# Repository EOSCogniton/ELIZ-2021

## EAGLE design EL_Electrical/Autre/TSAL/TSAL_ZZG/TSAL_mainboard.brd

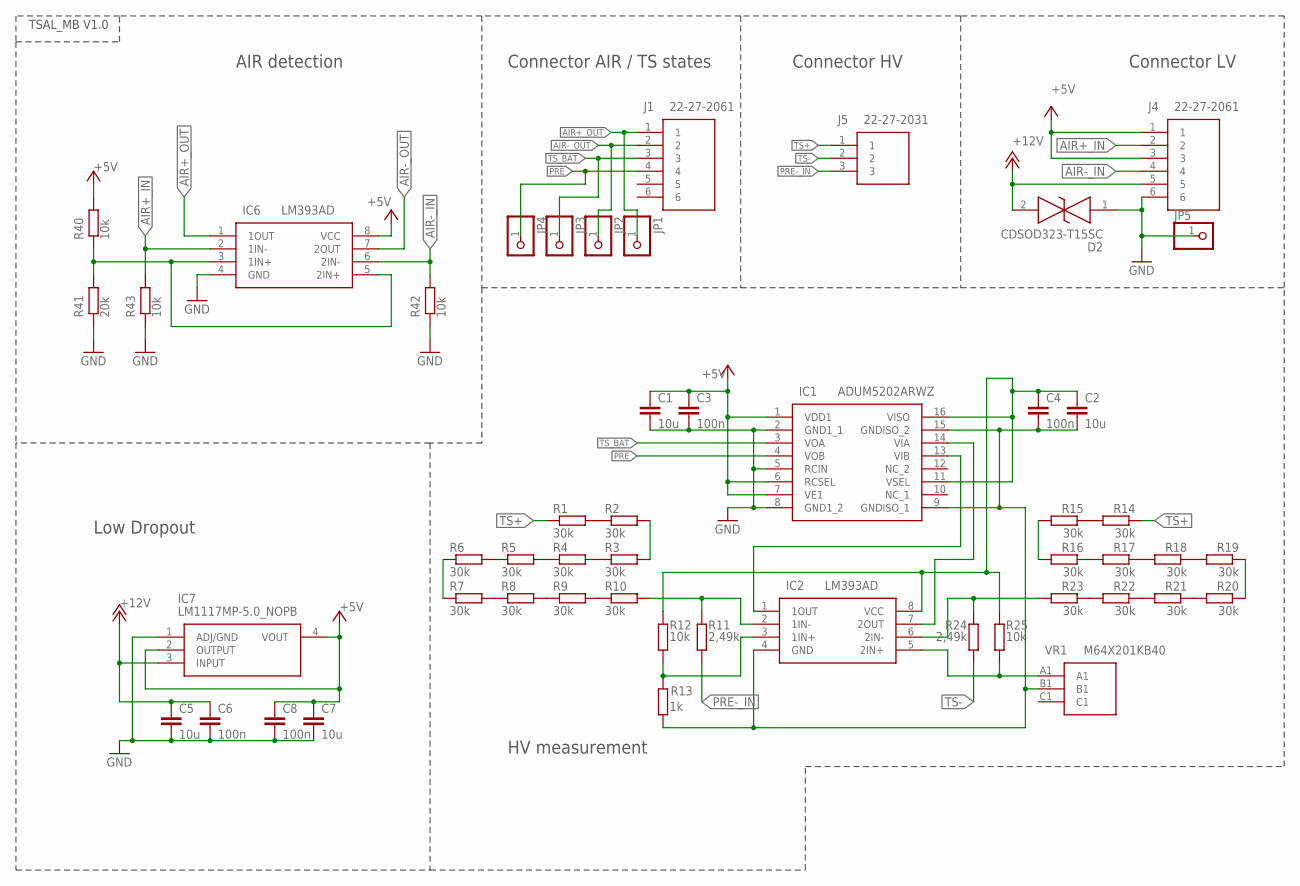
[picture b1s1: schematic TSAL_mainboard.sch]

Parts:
C1, C2, C5, C7: 10u; C1206
C3, C4, C6, C8: 100n; C0603
D2: CDSOD323-T15SC; SOD-323
IC1: ADUM5202ARWZ; SOIC127P1032X265-16N
IC2, IC6: LM393AD; SOIC127P600X175-8N
IC7: LM1117MP-5.0_NOPB; SOT230P700X180-4N
J1, J4: 22-27-2061; HDRV6W64P0X254_1X6_1524X580X11
J5: 22-27-2031; SHDR3W64P0X254_1X3_762X580X111
JP1, JP2, JP3, JP4, JP5: PINHD-1X1; 1X01
R1, R2, R3, R4, R5, R6, R7, R8, R9, R10, R14, R15, R16, R17, R18, R19, R20, R21, R22, R23: 30k; R1206
R11, R24: 2,49k; R0603
R12, R25, R40, R42, R43: 10k; R0603
R13: 1k; R1206
R41: 20k; R0603
VR1: M64X201KB40

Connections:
+5V: C1.1, C3.1, C7.1, C8.1, IC1.1 (VDD1), IC1.6 (RCSEL), IC1.7 (VE1), IC6.8 (VCC), IC7.2 (OUTPUT), IC7.4 (VOUT), J4.1, J4.3, R40.2
+12V: C5.1, C6.1, D2.2, IC7.3 (INPUT), J4.5
AIR+_IN: IC6.2 (1IN-), J4.2, R43.2
AIR+_OUT: IC6.1 (1OUT), J1.1, JP1.1
AIR-_IN: IC6.6 (2IN-), J4.4, R42.2
AIR-_OUT: IC6.7 (2OUT), J1.2, JP2.1
GND: C1.2, C3.2, C5.2, C6.2, C7.2, C8.2, D2.1, IC1.2 (GND1_1), IC1.5 (RCIN), IC1.8 (GND1_2), IC6.4 (GND), IC7.1 (ADJ/GND), J4.6, JP5.1, R41.1, R42.1, R43.1
unnamed: C2.1, C4.1, IC1.11 (VSEL), IC1.16 (VISO), IC2.8 (VCC), R12.1, R25.1
unnamed: R1.1, R2.2
unnamed: R2.1, R3.2
unnamed: R3.1, R4.2
unnamed: R4.1, R5.2
unnamed: R6.2, R7.1
unnamed: R7.2, R8.1
unnamed: R8.2, R9.1
unnamed: R9.2, R10.1
unnamed: R5.1, R6.1
unnamed: IC2.2 (1IN-), R10.2, R11.1
unnamed: IC2.3 (1IN+), R12.2, R13.1
unnamed: R14.1, R15.2
unnamed: R15.1, R16.2
unnamed: R16.1, R17.2
unnamed: R17.1, R18.2
unnamed: R19.2, R20.1
unnamed: R20.2, R21.1
unnamed: R21.2, R22.1
unnamed: R22.2, R23.1
unnamed: R18.1, R19.1
unnamed: IC2.6 (2IN-), R23.2, R24.1
unnamed: IC1.13 (VIB), IC2.1 (1OUT)
unnamed: IC2.5 (2IN+), R25.2, VR1.A1
unnamed: IC1.14 (VIA), IC2.7 (2OUT)
unnamed: IC6.3 (1IN+), IC6.5 (2IN+), R40.1, R41.2
unnamed: C2.2, C4.2, IC1.9 (GNDISO_1), IC1.15 (GNDISO_2), IC2.4 (GND), R13.2, VR1.B1
PRE: IC1.4 (VOB), J1.4, JP4.1
PRE-_IN: J5.3, R11.2
TS+: J5.1, R1.2, R14.2
TS-: J5.2, R24.2
TS_BAT: IC1.3 (VOA), J1.3, JP3.1

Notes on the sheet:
Low Dropout
HV measurement
TSAL_MB V1.0
Connector LV
Connector HV
Connector AIR / TS states
AIR detection

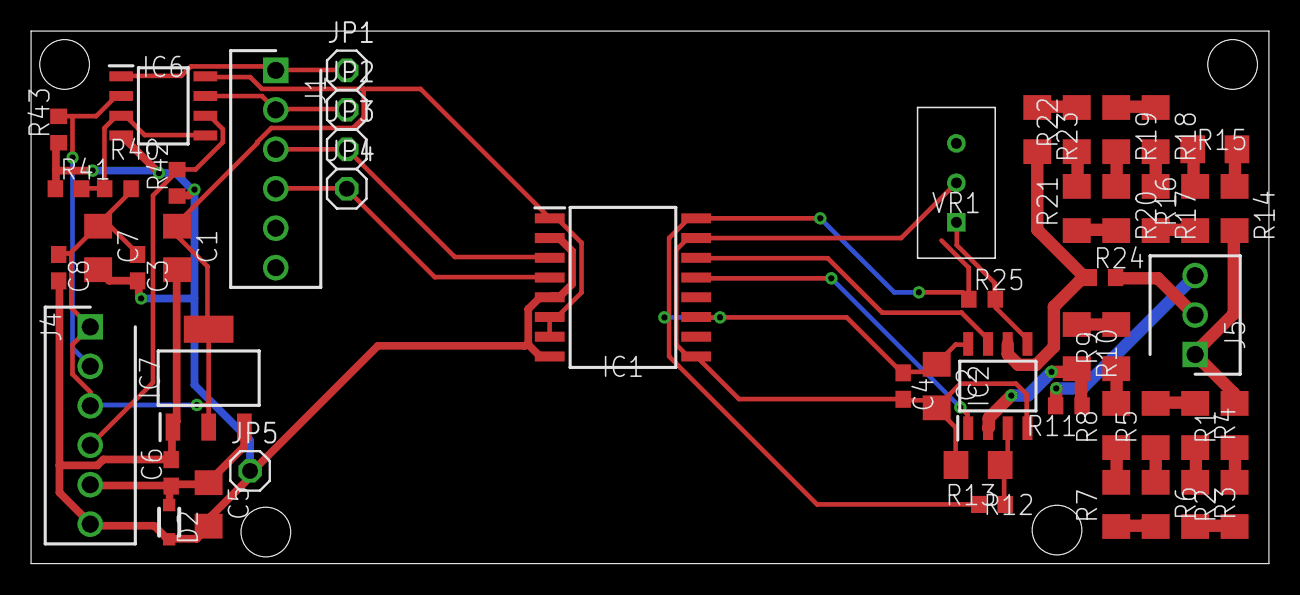
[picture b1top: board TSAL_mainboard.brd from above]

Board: 2 copper layers, 79.7 x 34.3 mm, 51 parts (0 on the bottom side), 39 nets.

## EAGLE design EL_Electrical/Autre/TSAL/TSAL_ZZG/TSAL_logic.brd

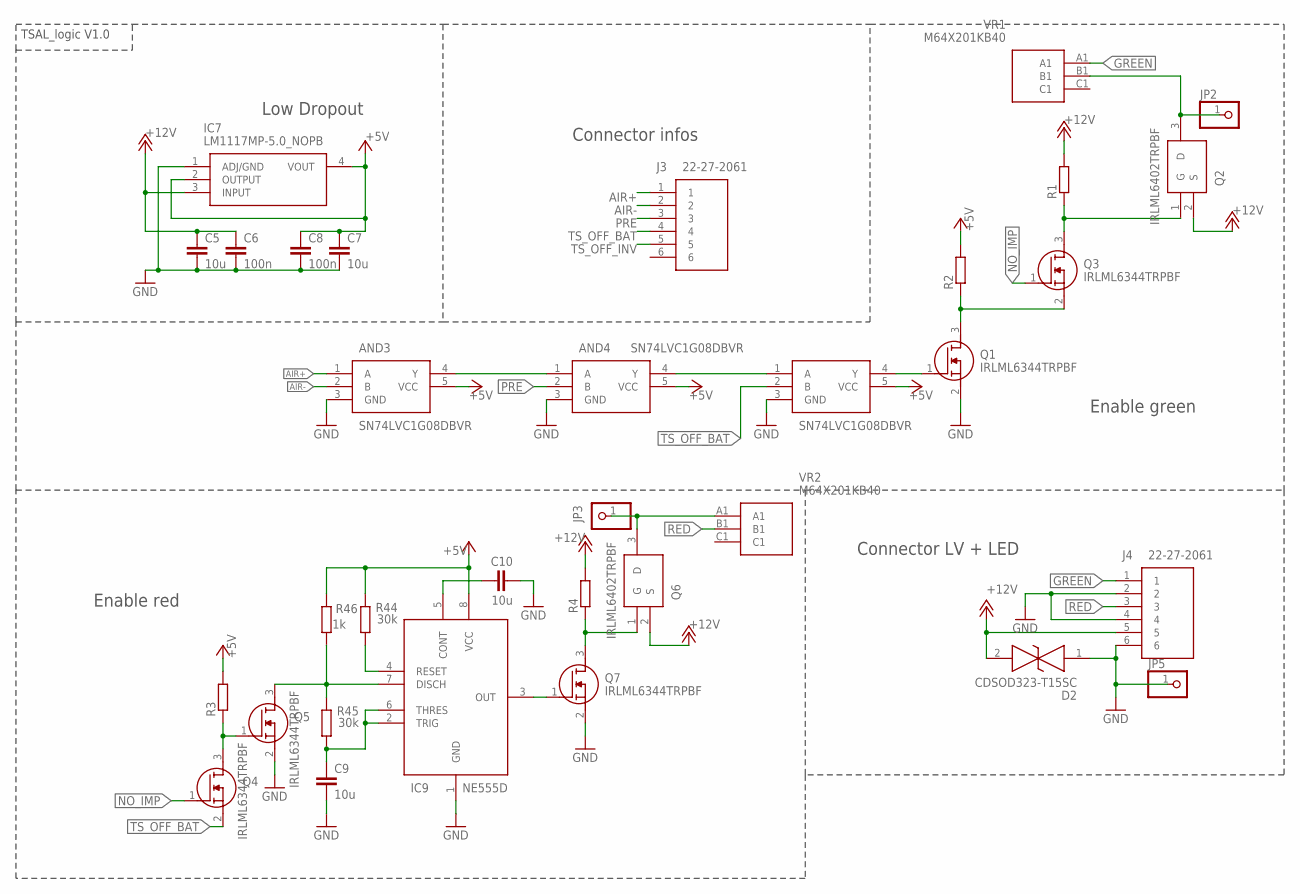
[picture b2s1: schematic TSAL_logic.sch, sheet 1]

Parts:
AND3, AND4, AND5: SN74LVC1G08DBVR; SOT95P280X145-5N
C5, C7, C9, C10: 10u; C1206
C6, C8: 100n; C0603
D2: CDSOD323-T15SC; SOD-323
IC7: LM1117MP-5.0_NOPB; SOT230P700X180-4N
IC9: NE555D; SOIC127P600X175-8N
J3, J4: 22-27-2061; HDRV6W64P0X254_1X6_1524X580X11
JP2, JP3, JP5: PINHD-1X1; 1X01
Q1, Q3, Q4, Q5, Q7: IRLML6344TRPBF; SOT95P237X112-3N
Q2, Q6: IRLML6402TRPBF; SOT95P237X112-3N
R1, R2, R3, R4: R-EU_R0603; R0603
R44, R45: 30k; R1206
R46: 1k; R1206
VR1, VR2: M64X201KB40

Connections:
12VN$2: Q2.1 (G), Q3.3 (D), R1.1
12VN$5: Q6.1 (G), Q7.3 (D), R4.1
12VN$29: JP2.1, Q2.3 (D), VR1.B1
+5V: AND3.5 (VCC), AND4.5 (VCC), AND5.5 (VCC), C7.1, C8.1, IC7.2 (OUTPUT), IC7.4 (VOUT), IC9.8 (VCC), R2.2, R3.2, R44.1, R46.1; also elsewhere on the board
+12V: C5.1, C6.1, D2.2, IC7.3 (INPUT), J4.5, Q2.2 (S), Q6.2 (S), R1.2, R4.2
AIR+: AND3.1 (A), J3.1; also elsewhere on the board
AIR-: AND3.2 (B), J3.2; also elsewhere on the board
GND: AND3.3 (GND), AND4.3 (GND), AND5.3 (GND), C5.2, C6.2, C7.2, C8.2, C9.2, C10.2, D2.1, IC7.1 (ADJ/GND), IC9.1 (GND), J4.2, J4.4, J4.6, JP5.1, Q1.2 (S), Q5.2 (S), Q7.2 (S); also elsewhere on the board
GREEN: J4.1, VR1.A1
unnamed: Q1.3 (D), Q3.2 (S), R2.1
unnamed: JP3.1, Q6.3 (D), VR2.A1
unnamed: Q4.3 (D), Q5.1 (G), R3.1
unnamed: IC9.3 (OUT), Q7.1 (G)
unnamed: AND4.4 (Y), AND5.1 (A)
unnamed: AND3.4 (Y), AND4.1 (A)
unnamed: AND5.4 (Y), Q1.1 (G)
unnamed: IC9.7 (DISCH), Q5.3 (D), R45.2, R46.2
unnamed: C9.1, IC9.2 (TRIG), IC9.6 (THRES), R45.1
unnamed: IC9.4 (RESET), R44.2
unnamed: C10.1, IC9.5 (CONT)
NO_IMP: Q3.1 (G), Q4.1 (G); also elsewhere on the board
PRE: AND4.2 (B), J3.3
RED: J4.3, VR2.B1
TS_OFF_BAT: AND5.2 (B), J3.4, Q4.2 (S); also elsewhere on the board
TS_OFF_INV: J3.5; also elsewhere on the board

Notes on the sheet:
Enable green
Enable red
Low Dropout
Connector infos
TSAL_logic V1.0
Connector LV + LED

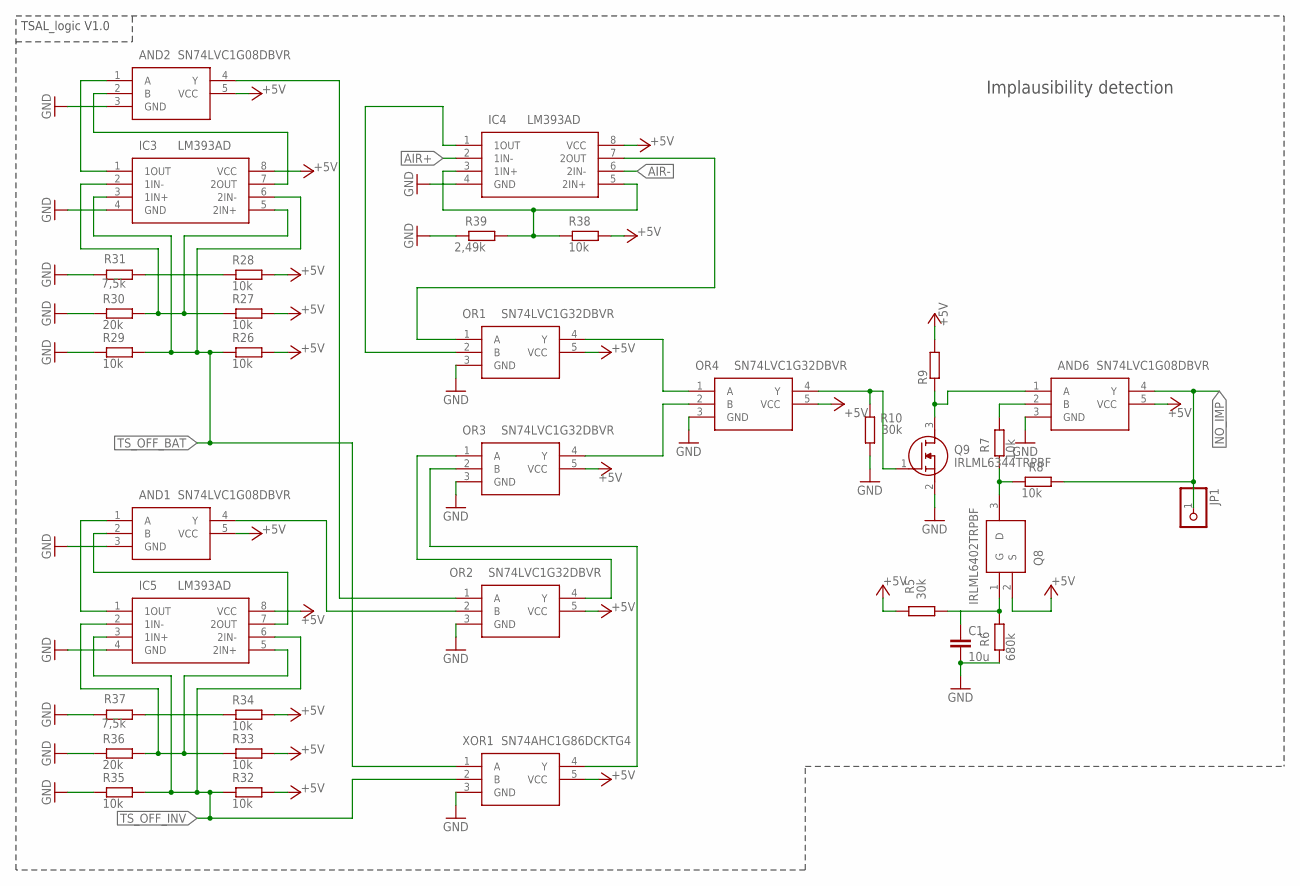
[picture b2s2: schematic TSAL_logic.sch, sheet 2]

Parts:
AND1, AND2, AND6: SN74LVC1G08DBVR; SOT95P280X145-5N
C1: 10u; C1206
IC3, IC4, IC5: LM393AD; SOIC127P600X175-8N
JP1: PINHD-1X1; 1X01
OR1, OR2, OR3, OR4: SN74LVC1G32DBVR; SOT95P280X145-5N
Q8: IRLML6402TRPBF; SOT95P237X112-3N
Q9: IRLML6344TRPBF; SOT95P237X112-3N
R5, R10: 30k; R1206
R6: 680k; R0603
R7, R8, R26, R27, R28, R29, R32, R33, R34, R35, R38: 10k; R0603
R9: R-EU_R0603; R0603
R30, R36: 20k; R0603
R31, R37: 7,5k; R0805
R39: 2,49k; R0603
XOR1: SN74AHC1G86DCKTG4; SOT65P210X110-5N

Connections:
+5V: AND1.5 (VCC), AND2.5 (VCC), AND6.5 (VCC), IC3.8 (VCC), IC4.8 (VCC), IC5.8 (VCC), OR1.5 (VCC), OR2.5 (VCC), OR3.5 (VCC), OR4.5 (VCC), Q8.2 (S), R5.1, R9.2, R26.2, R27.2, R28.2, R32.2, R33.2, R34.2, R38.2, XOR1.5 (VCC); also elsewhere on the board
AIR+: IC4.2 (1IN-); also elsewhere on the board
AIR-: IC4.6 (2IN-); also elsewhere on the board
GND: AND1.3 (GND), AND2.3 (GND), AND6.3 (GND), C1.2, IC3.4 (GND), IC4.4 (GND), IC5.4 (GND), OR1.3 (GND), OR2.3 (GND), OR3.3 (GND), OR4.3 (GND), Q9.2 (S), R6.1, R10.2, R29.1, R30.1, R31.1, R35.1, R36.1, R37.1, R39.1, XOR1.3 (GND); also elsewhere on the board
unnamed: OR2.4 (Y), OR3.1 (A)
unnamed: OR4.4 (Y), Q9.1 (G), R10.1
unnamed: C1.1, Q8.1 (G), R5.2, R6.2
unnamed: AND6.2 (B), R7.2
unnamed: Q8.3 (D), R7.1, R8.1
unnamed: IC4.7 (2OUT), OR1.1 (A)
unnamed: AND1.4 (Y), OR2.2 (B)
unnamed: OR3.2 (B), XOR1.4 (Y)
unnamed: OR1.4 (Y), OR4.1 (A)
unnamed: AND6.1 (A), Q9.3 (D), R9.1
unnamed: R28.1, R31.2
unnamed: IC3.2 (1IN-), IC3.5 (2IN+), R27.1, R30.2
unnamed: AND2.1 (A), IC3.1 (1OUT)
unnamed: AND2.2 (B), IC3.7 (2OUT)
unnamed: R34.1, R37.2
unnamed: IC5.2 (1IN-), IC5.5 (2IN+), R33.1, R36.2
unnamed: AND1.2 (B), IC5.7 (2OUT)
unnamed: AND1.1 (A), IC5.1 (1OUT)
unnamed: IC4.3 (1IN+), IC4.5 (2IN+), R38.1, R39.2
unnamed: IC4.1 (1OUT), OR1.2 (B)
unnamed: AND2.4 (Y), OR2.1 (A)
unnamed: OR3.4 (Y), OR4.2 (B)
NO_IMP: AND6.4 (Y), JP1.1, R8.2; also elsewhere on the board
TS_OFF_BAT: IC3.3 (1IN+), IC3.6 (2IN-), R26.1, R29.2, XOR1.1 (A); also elsewhere on the board
TS_OFF_INV: IC5.3 (1IN+), IC5.6 (2IN-), R32.1, R35.2, XOR1.2 (B); also elsewhere on the board

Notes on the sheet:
Implausibility detection
TSAL_logic V1.0

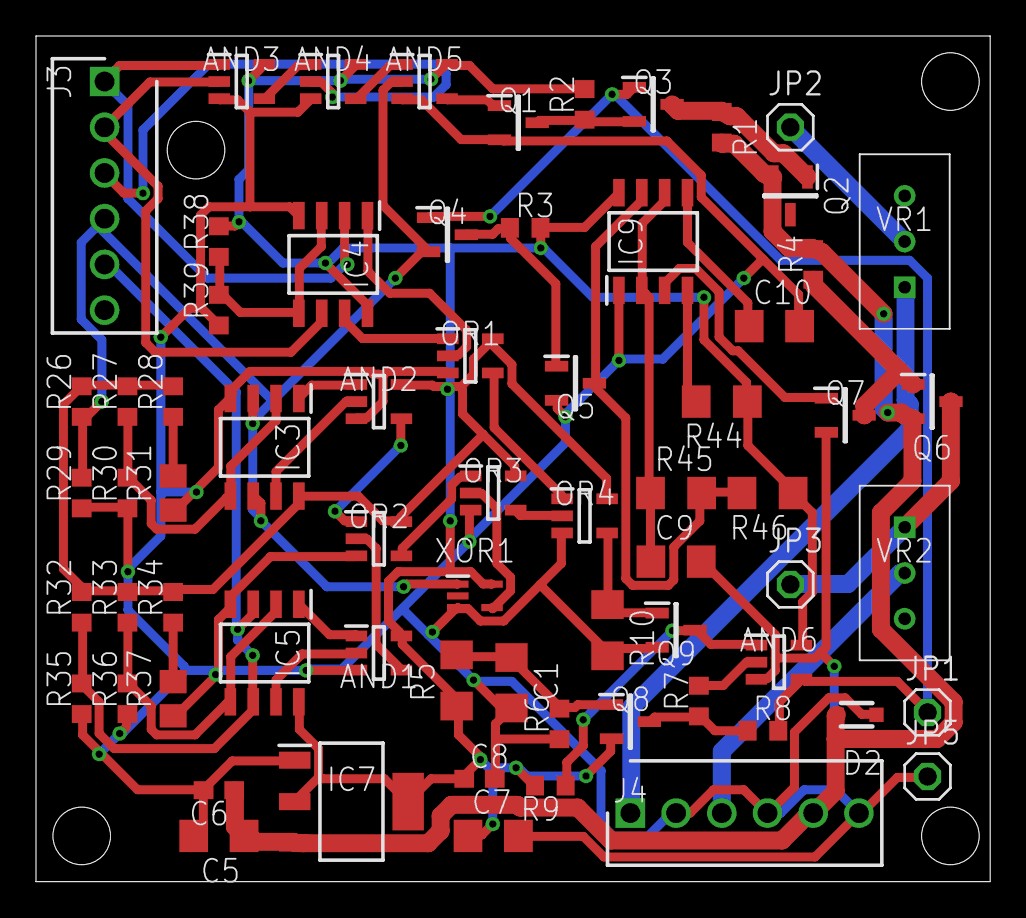
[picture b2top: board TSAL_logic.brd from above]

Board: 2 copper layers, 53.0 x 47.0 mm, 68 parts (0 on the bottom side), 47 nets.

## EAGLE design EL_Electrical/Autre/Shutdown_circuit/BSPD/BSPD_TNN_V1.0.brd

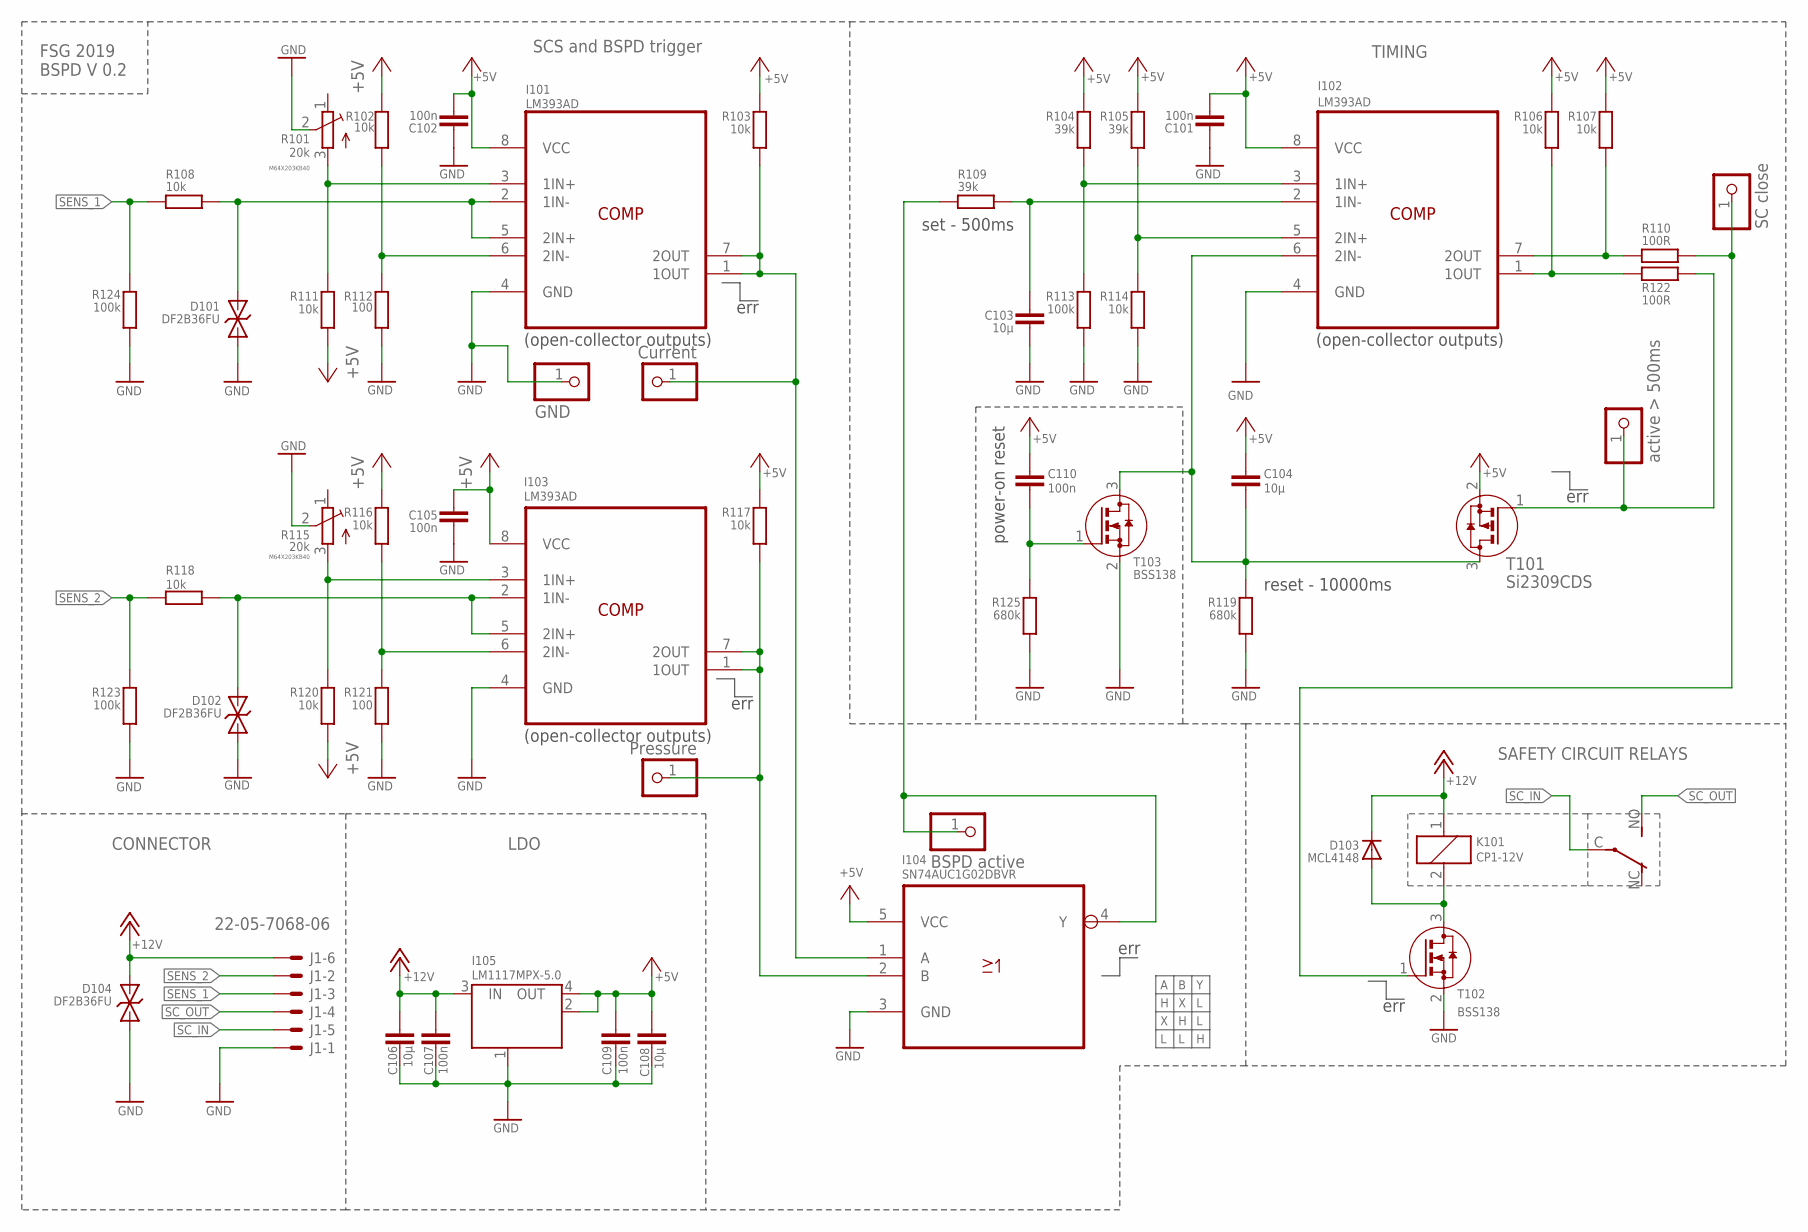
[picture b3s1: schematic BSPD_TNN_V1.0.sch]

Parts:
C101, C102, C105, C107, C109, C110: 100n; C0603
C103, C106, C108: 10µ; C1206
C104: 10µ; C1206K
D101, D102, D104: DF2B36FU; SOD323
D103: MCL4148; MICROMELF
I101, I102, I103: LM393AD; SOIC127P600X175-8N
I104: SN74AUC1G02DBVR; SOT95P280X145-5N
I105: LM1117MPX-5.0; LINEAR_SOT223
J1: 22-05-7068-06; 7395-06
JP1: Pressure; 1X01
JP2: Current; 1X01
JP3: BSPD active; 1X01
JP4: active > 500ms; 1X01
JP5: SC close; 1X01
JP6: GND; 1X01
K101: CP1-12V; CP1
R101, R115: 20k; M64X201KB40
R102, R103, R106, R107, R108, R111, R114, R116, R117, R118, R120: 10k; R0603
R104, R105, R109: 39k; R0603
R110, R122: 100R; R0603
R112, R121: 100; R0603
R113, R123, R124: 100k; R0603
R119, R125: 680k; R0603
T101: Si2309CDS; SOT-23
T102, T103: BSS138; SOT-23

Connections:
+5V: C101.2, C102.2, C104.1, C105.2, C108.1, C109.2, C110.1, I101.8 (VCC), I102.8 (VCC), I103.8 (VCC), I104.5 (VCC), I105.2 (OUT), I105.4 (OUT), R102.1, R103.1, R104.2, R105.2, R106.2, R107.2, R111.2, R116.1, R117.1, R120.2, T101.2 (S)
+12V: C106.1, C107.1, D103.C, D104.2 (C), I105.3 (IN), J1.6, K101.1
BRAKE_F: D101.2 (C), I101.2 (1IN-), I101.5 (2IN+), R108.2
DF: D102.2 (C), I103.2 (1IN-), I103.5 (2IN+), R118.2
GND: C101.1, C102.1, C103.2, C105.1, C106.2, C107.2, C108.2, C109.1, D101.1 (A), D102.1 (A), D104.1 (A), I101.4 (GND), I102.4 (GND), I103.4 (GND), I104.3 (GND), I105.1 (GND/ADJ), J1.1, JP6.1, R101.2 (M), R112.2, R113.1, R114.1, R115.2 (M), R119.1, R121.2, R123.1, R124.1, R125.1, T102.2 (S), T103.2 (S)
unnamed: I102.5 (2IN+), R105.1, R114.2
unnamed: I103.1 (1OUT), I103.7 (2OUT), I104.2 (B), JP1.1, R117.2
unnamed: I101.1 (1OUT), I101.7 (2OUT), I104.1 (A), JP2.1, R103.2
unnamed: I102.1 (1OUT), R106.1, R122.2
unnamed: C110.2, R125.2, T103.1 (G)
unnamed: I101.3 (1IN+), R101.3 (A), R111.1
unnamed: C104.2, I102.6 (2IN-), R119.2, T101.3 (D), T103.3 (D)
unnamed: I103.3 (1IN+), R115.3 (A), R120.1
unnamed: JP5.1, R110.1, T102.1 (G)
unnamed: D103.A, K101.2, T102.3 (D)
unnamed: C103.1, I102.2 (1IN-), R109.1
unnamed: I102.3 (1IN+), R104.1, R113.2
unnamed: I101.6 (2IN-), R102.2, R112.1
unnamed: I102.7 (2OUT), R107.1, R110.2
unnamed: I103.6 (2IN-), R116.2, R121.1
unnamed: JP4.1, R122.1, T101.1 (G)
unnamed: I104.4 (Y), JP3.1, R109.2
SC_IN: J1.5, K101.C
SC_OUT: J1.4, K101.NO (S)
SENS_1: J1.3, R108.1, R124.2
SENS_2: J1.2, R118.1, R123.2

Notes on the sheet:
COMP
M64X203KB40
FSG 2019 BSPD V 0.2
CONNECTOR
LDO
SAFETY CIRCUIT RELAYS
err
TIMING
SCS and BSPD trigger
power-on reset
set - 500ms
reset - 10000ms
(open-collector outputs)

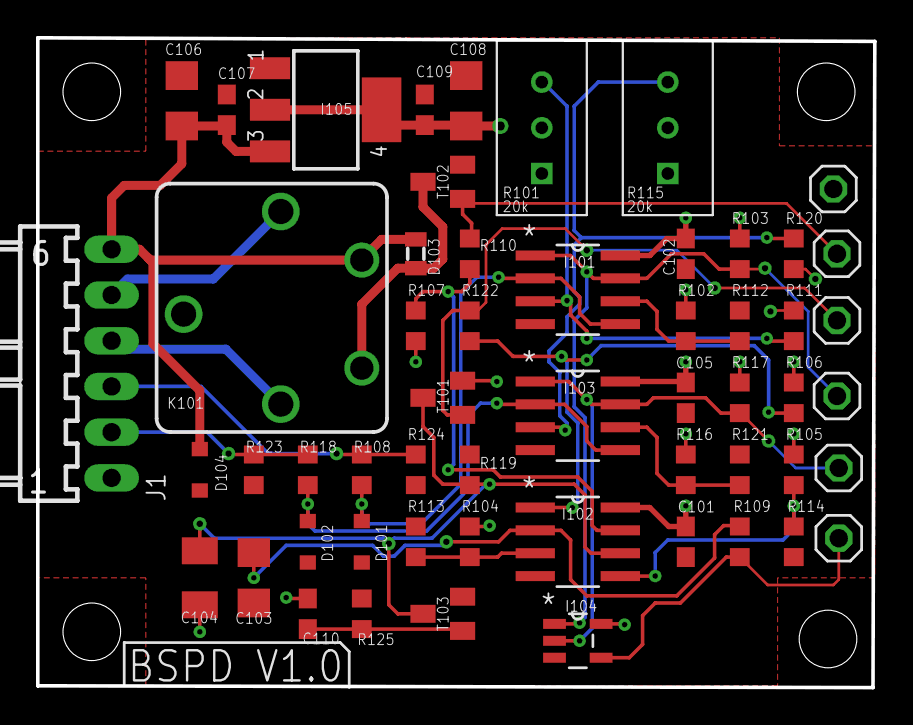
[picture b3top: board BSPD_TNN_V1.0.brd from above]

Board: 2 copper layers, 46.5 x 36.1 mm, 55 parts (0 on the bottom side), 26 nets.

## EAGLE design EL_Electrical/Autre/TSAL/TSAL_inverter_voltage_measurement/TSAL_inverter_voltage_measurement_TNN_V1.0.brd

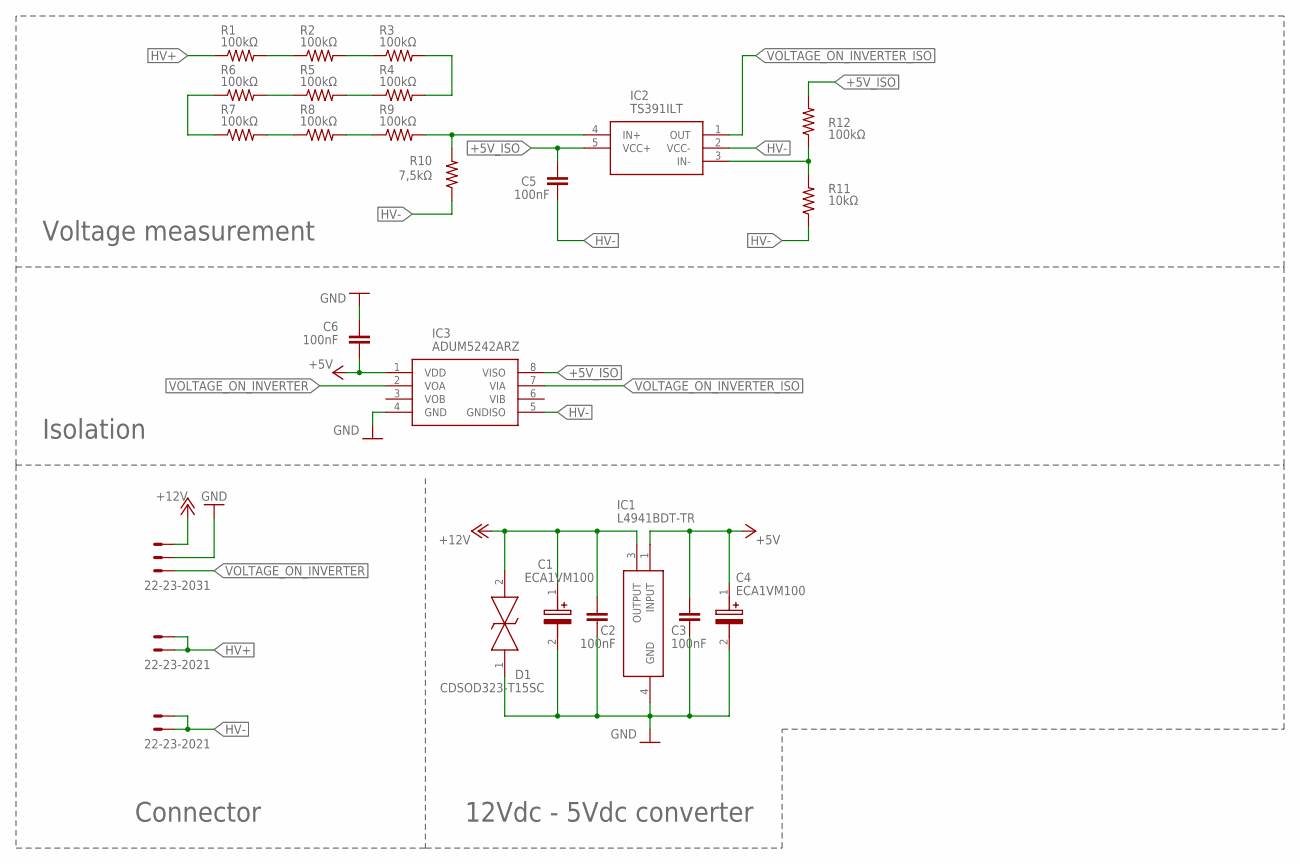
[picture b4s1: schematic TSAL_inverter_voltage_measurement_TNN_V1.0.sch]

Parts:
C1, C4: ECA1VM100; CAPPRD200W55D525H1200
C2, C3, C5, C6: 100nF; C0603
D1: CDSOD323-T15SC; SOD-323
HV+: 22-23-2021
HV-: 22-23-2021
IC1: L4941BDT-TR; TO228P972X240-3N
IC2: TS391ILT; SOT95P280X145-5N
IC3: ADUM5242ARZ; SOIC127P600X175-8N
LOW_VOLTAGE: 22-23-2031
R1, R2, R3, R4, R5, R6, R7, R8, R9, R12: 100kΩ; R0603
R10: 7,5kΩ; R0603
R11: 10kΩ; R0603

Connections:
+5V: C3.2, C4.1 (+), C6.1, IC1.1 (INPUT), IC3.1 (VDD)
+5V_ISO: C5.2, IC2.5 (VCC+), IC3.8 (VISO), R12.2
+12V: C1.1 (+), C2.2, D1.2, IC1.3 (OUTPUT), LOW_VOLTAGE.3
GND: C1.2 (-), C2.1, C3.1, C4.2 (-), C6.2, D1.1, IC1.4 (GND), IC3.4 (GND), LOW_VOLTAGE.2
HV+: HV+.1, HV+.2, R1.1
HV-: C5.1, HV-.1, HV-.2, IC2.2 (VCC-), IC3.5 (GNDISO), R10.1, R11.1
unnamed: R1.2, R2.1
unnamed: R2.2, R3.1
unnamed: R3.2, R4.2
unnamed: R4.1, R5.2
unnamed: R5.1, R6.2
unnamed: R6.1, R7.1
unnamed: R7.2, R8.1
unnamed: R8.2, R9.1
unnamed: IC2.4 (IN+), R9.2, R10.2
unnamed: IC2.3 (IN-), R11.2, R12.1
VOLTAGE_ON_INVERTER: IC3.2 (VOA), LOW_VOLTAGE.1
VOLTAGE_ON_INVERTER_ISO: IC2.1 (OUT), IC3.7 (VIA)

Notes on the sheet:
Connector
12Vdc - 5Vdc converter
Isolation
Voltage measurement

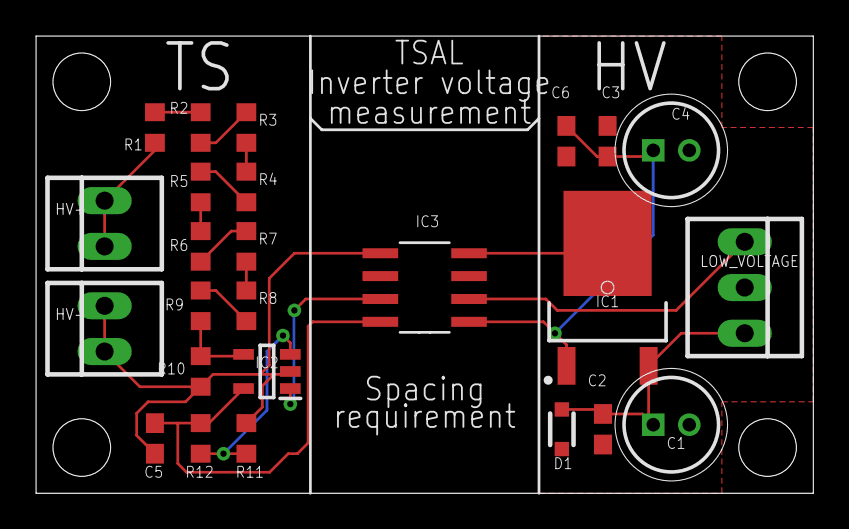
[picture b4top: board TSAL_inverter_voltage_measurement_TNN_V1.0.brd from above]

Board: 2 copper layers, 43.2 x 25.4 mm, 25 parts (0 on the bottom side), 18 nets.

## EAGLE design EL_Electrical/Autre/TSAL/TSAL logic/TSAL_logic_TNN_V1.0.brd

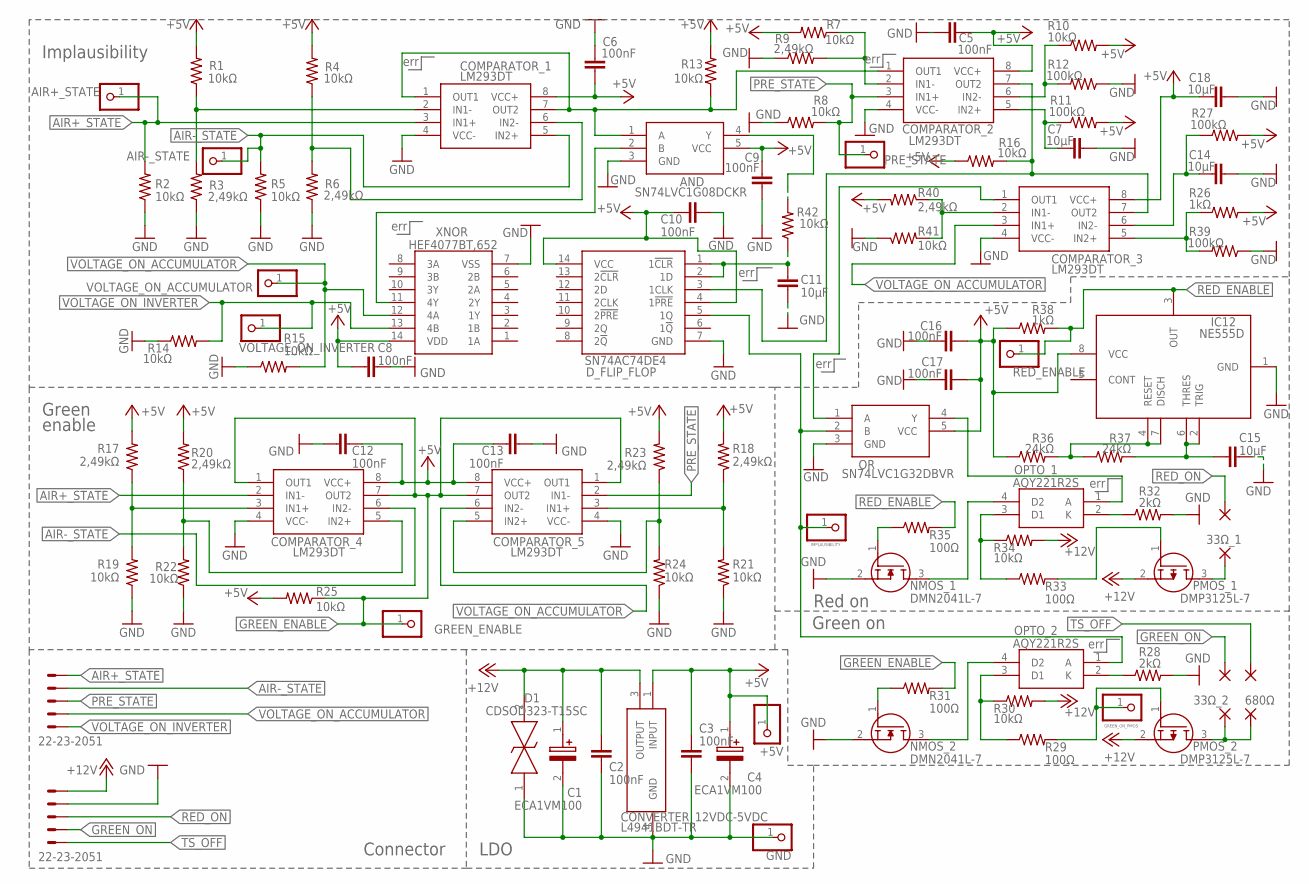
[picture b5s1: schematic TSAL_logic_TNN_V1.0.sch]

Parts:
33Ω_1, 33Ω_1_, 33Ω_2, 33Ω_2_, 680Ω, 680Ω_: 1,6/0,8
+5V: PINHD-1X1; 1X01
AIR+_STATE: PINHD-1X1; 1X01
AIR-_STATE: PINHD-1X1; 1X01
AND: SN74LVC1G08DCKR; SOT65P210X110-5N
C1, C4: ECA1VM100; CAPPRD200W55D525H1200
C2, C3, C5, C6, C8, C9, C10, C12, C13, C16, C17: 100nF; C0603
C7, C11, C14, C15, C18: 10μF; C0603
COMPARATOR_1, COMPARATOR_2, COMPARATOR_3, COMPARATOR_4, COMPARATOR_5: LM293DT; SOIC127P600X175-8N
CONTACTOR_STATE_AND_VOLTAGE_MEASUREMENT: 22-23-2051
CONVERTER_12VDC-5VDC: L4941BDT-TR; TO228P972X240-3N
D1: CDSOD323-T15SC; SOD-323
D_FLIP_FLOP: SN74AC74DE4; SOIC127P600X175-14N
GND: PINHD-1X1; 1X01
GREEN_ENABLE: PINHD-1X1; 1X01
GREEN_ON_PMOS: PINHD-1X1; 1X01
IC12: NE555D; SOIC127P600X175-8N
IMPLAUSIBILITY: PINHD-1X1; 1X01
NMOS_1, NMOS_2: DMN2041L-7; SOT96P240X110-3N
OPTO_1, OPTO_2: AQY221R2S; SOP254P680X230-4N
OR: SN74LVC1G32DBVR; SOT95P280X145-5N
PMOS_1, PMOS_2: DMP3125L-7; SOT96P240X110-3N
PRE_STATE: PINHD-1X1; 1X01
R1, R2, R4, R5, R7, R8, R10, R13, R14, R15, R16, R19, R21, R22, R24, R25, R30, R34, R41, R42: 10kΩ; R0603
R3, R6, R9, R17, R18, R20, R23, R40: 2,49kΩ; R0603
R11, R12, R27, R39: 100kΩ; R0603
R26, R38: 1kΩ; R0603
R28, R32: 2kΩ; R0603
R29, R31, R33, R35: 100Ω; R0603
R36, R37: 24kΩ; R0603
RED_ENABLE: PINHD-1X1; 1X01
TSAL_LED_AND_POWER: 22-23-2051
VOLTAGE_ON_ACCUMULATOR: PINHD-1X1; 1X01
VOLTAGE_ON_INVERTER: PINHD-1X1; 1X01
XNOR: HEF4077BT,652; SOIC127P600X175-14N

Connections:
+5V: +5V.1, AND.5 (VCC), C3.1, C4.1 (+), C5.2, C6.2, C8.1, C9.1, C10.1, C12.1, C13.1, C16.1, C17.1, C18.1, COMPARATOR_1.8 (VCC+), COMPARATOR_2.8 (VCC+), COMPARATOR_3.8 (VCC+), COMPARATOR_4.8 (VCC+), COMPARATOR_5.8 (VCC+), CONVERTER_12VDC-5VDC.1 (INPUT), D_FLIP_FLOP.4 (1!PRE), D_FLIP_FLOP.14 (VCC), IC12.8 (VCC), OR.5 (VCC), R1.2, R4.2, R7.2, R10.2, R11.2, R13.2, R16.1, R17.2, R18.2, R20.2, R23.2, R25.2, R26.2, R27.2, R36.1, R38.1, R40.2, XNOR.14 (VDD)
+12V: C1.1 (+), C2.1, CONVERTER_12VDC-5VDC.3 (OUTPUT), D1.2, PMOS_1.2 (S), PMOS_2.2 (S), R30.2, R34.2, TSAL_LED_AND_POWER.5
AIR+_STATE: AIR+_STATE.1, COMPARATOR_1.3 (IN1+), COMPARATOR_4.2 (IN1-), CONTACTOR_STATE_AND_VOLTAGE_MEASUREMENT.5, R2.2
AIR-_STATE: AIR-_STATE.1, COMPARATOR_1.5 (IN2+), COMPARATOR_4.6 (IN2-), CONTACTOR_STATE_AND_VOLTAGE_MEASUREMENT.4, R5.2
GND: AND.3 (GND), C1.2 (-), C2.2, C3.2, C4.2 (-), C5.1, C6.1, C7.2, C8.2, C9.2, C10.2, C11.2, C12.2, C13.2, C14.2, C15.2, C16.2, C17.2, C18.2, COMPARATOR_1.4 (VCC-), COMPARATOR_2.4 (VCC-), COMPARATOR_3.4 (VCC-), COMPARATOR_4.4 (VCC-), COMPARATOR_5.4 (VCC-), CONVERTER_12VDC-5VDC.4 (GND), D1.1, D_FLIP_FLOP.7 (GND), GND.1, IC12.1 (GND), NMOS_1.2 (S), NMOS_2.2 (S), OR.3 (GND), R2.1, R3.1, R5.1, R6.1, R8.1, R9.1, R12.1, R14.1, R15.1, R19.1, R21.1, R22.1, R24.1, R28.2, R32.2, R39.1, R41.1, TSAL_LED_AND_POWER.4, XNOR.7 (VSS)
GREEN_ENABLE: COMPARATOR_4.1 (OUT1), COMPARATOR_4.7 (OUT2), COMPARATOR_5.1 (OUT1), COMPARATOR_5.7 (OUT2), GREEN_ENABLE.1, R25.1, R31.2
GREEN_ON: 33Ω_2_.1, TSAL_LED_AND_POWER.2
IMPLAUSIBILITY: D_FLIP_FLOP.5 (1Q), IMPLAUSIBILITY.1, OPTO_2.1 (A), OR.2 (B)
unnamed: COMPARATOR_1.2 (IN1-), R1.1, R3.2
unnamed: AND.1 (A), COMPARATOR_1.1 (OUT1), COMPARATOR_1.7 (OUT2), COMPARATOR_2.1 (OUT1), R13.1
unnamed: COMPARATOR_1.6 (IN2-), R4.1, R6.2
unnamed: COMPARATOR_2.2 (IN1-), R7.1, R9.2
unnamed: COMPARATOR_2.6 (IN2-), R10.1, R12.2
unnamed: C7.1, COMPARATOR_2.5 (IN2+), R11.1
unnamed: COMPARATOR_2.7 (OUT2), COMPARATOR_3.7 (OUT2), D_FLIP_FLOP.3 (1CLK), R16.2
unnamed: AND.2 (B), XNOR.11 (4Y)
unnamed: COMPARATOR_5.5 (IN2+), R23.1, R24.2
unnamed: COMPARATOR_5.3 (IN1+), R18.1, R21.2
unnamed: COMPARATOR_4.3 (IN1+), R17.1, R19.2
unnamed: COMPARATOR_4.5 (IN2+), R20.1, R22.2
unnamed: COMPARATOR_3.5 (IN2+), R26.1, R39.2
unnamed: 33Ω_2.1, 680Ω.1, PMOS_2.3 (D)
unnamed: OPTO_2.2 (K), R28.1
unnamed: 33Ω_1.1, PMOS_1.3 (D)
unnamed: NMOS_2.3 (D), OPTO_2.4 (D2)
unnamed: OPTO_2.3 (D1), R29.1, R30.1
unnamed: GREEN_ON_PMOS.1, PMOS_2.1 (G), R29.2
unnamed: NMOS_2.1 (G), R31.1
unnamed: NMOS_1.3 (D), OPTO_1.4 (D2)
unnamed: OPTO_1.3 (D1), R33.1, R34.1
unnamed: PMOS_1.1 (G), R33.2
unnamed: NMOS_1.1 (G), R35.1
unnamed: OPTO_1.2 (K), R32.1
unnamed: COMPARATOR_3.1 (OUT1), OR.1 (A)
unnamed: OPTO_1.1 (A), OR.4 (Y)
unnamed: C14.1, COMPARATOR_3.6 (IN2-), R27.1
unnamed: C15.1, IC12.2 (TRIG), IC12.6 (THRES), R37.2
unnamed: IC12.4 (RESET), IC12.7 (DISCH), R36.2, R37.1
unnamed: COMPARATOR_3.2 (IN1-), R40.1, R41.2
unnamed: C11.1, D_FLIP_FLOP.1 (1!CLR), D_FLIP_FLOP.2 (1D), R42.1
unnamed: AND.4 (Y), R42.2
PRE_STATE: COMPARATOR_2.3 (IN1+), COMPARATOR_5.2 (IN1-), CONTACTOR_STATE_AND_VOLTAGE_MEASUREMENT.3, PRE_STATE.1, R8.2
RED_ENABLE: IC12.3 (OUT), R35.2, R38.2, RED_ENABLE.1
RED_ON: 33Ω_1_.1, TSAL_LED_AND_POWER.3
TS_OFF: 680Ω_.1, TSAL_LED_AND_POWER.1
VOLTAGE_ON_ACCUMULATOR: COMPARATOR_3.3 (IN1+), COMPARATOR_5.6 (IN2-), CONTACTOR_STATE_AND_VOLTAGE_MEASUREMENT.2, R15.2, VOLTAGE_ON_ACCUMULATOR.1, XNOR.12 (4A)
VOLTAGE_ON_INVERTER: CONTACTOR_STATE_AND_VOLTAGE_MEASUREMENT.1, R14.2, VOLTAGE_ON_INVERTER.1, XNOR.13 (4B)

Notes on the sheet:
Implausibility
Green enable
Connector
LDO
Green on
Red on
err

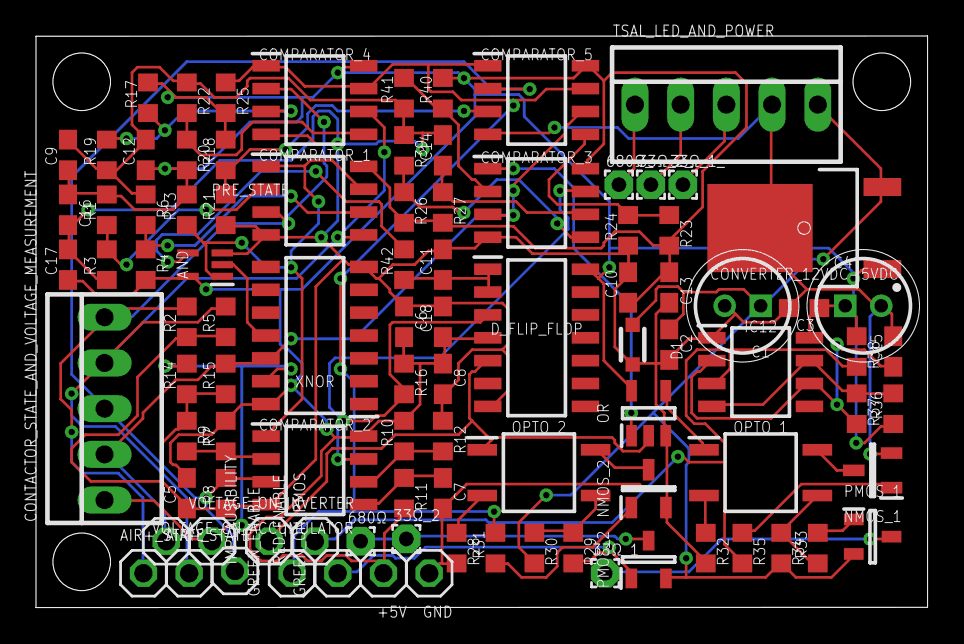
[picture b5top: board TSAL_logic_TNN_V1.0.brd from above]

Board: 2 copper layers, 49.5 x 31.8 mm, 97 parts (0 on the bottom side), 47 nets.

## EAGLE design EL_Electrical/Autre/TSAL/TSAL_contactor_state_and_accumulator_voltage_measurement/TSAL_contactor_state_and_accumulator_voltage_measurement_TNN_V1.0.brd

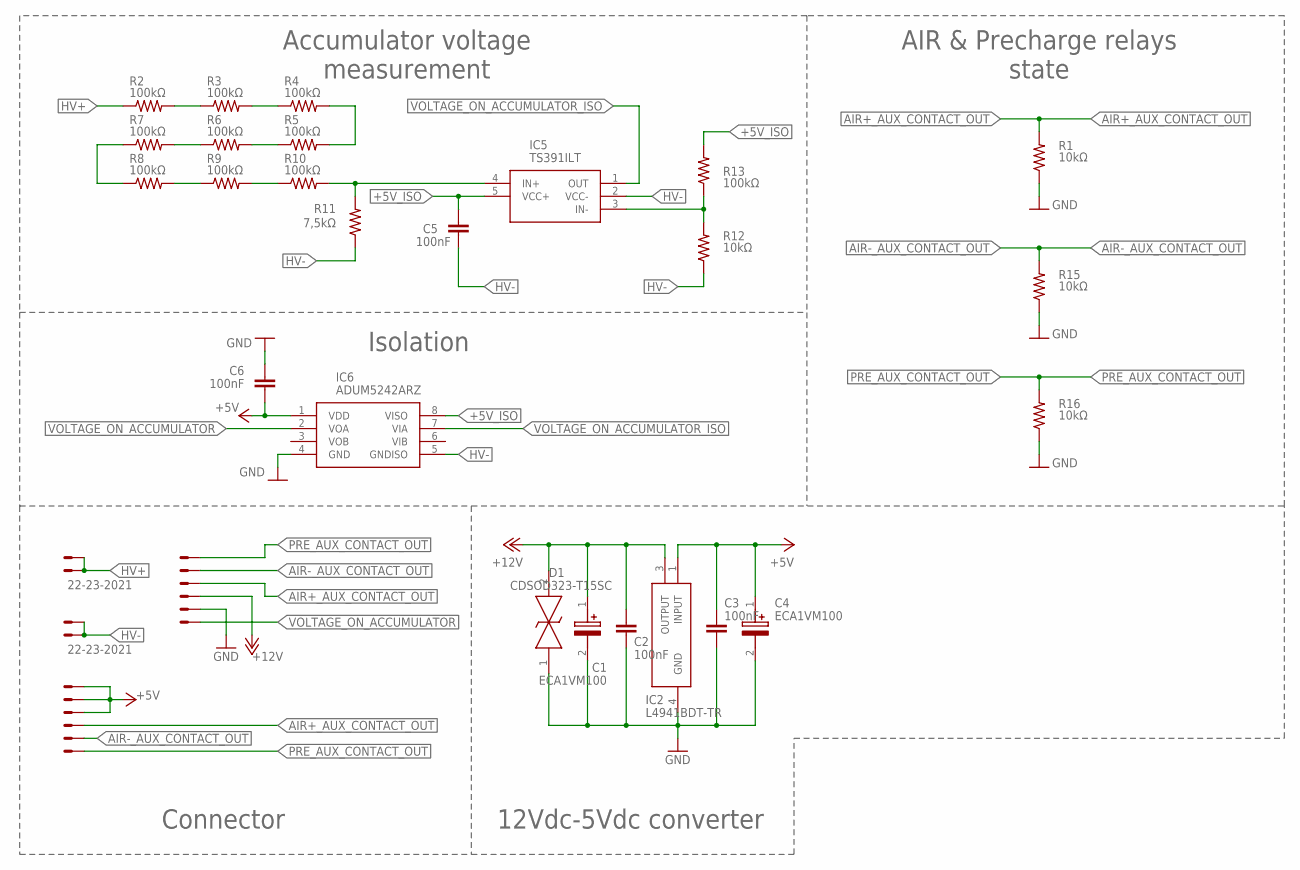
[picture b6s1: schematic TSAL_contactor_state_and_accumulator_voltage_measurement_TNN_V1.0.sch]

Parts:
AUX_CONTACT: 22-23-2061
C1, C4: ECA1VM100; CAPPRD200W55D525H1200
C2, C3, C5, C6: 100nF; C0603
D1: CDSOD323-T15SC; SOD-323
HV+: 22-23-2021
HV-: 22-23-2021
IC2: L4941BDT-TR; TO228P972X240-3N
IC5: TS391ILT; SOT95P280X145-5N
IC6: ADUM5242ARZ; SOIC127P600X175-8N
POWER_AND_TSAL_SIGNAL: 22-23-2061
R1, R12, R15, R16: 10kΩ; R0603
R2, R3, R4, R5, R6, R7, R8, R9, R10, R13: 100kΩ; R0603
R11: 7,5kΩ; R0603

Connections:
+5V: AUX_CONTACT.4, AUX_CONTACT.5, AUX_CONTACT.6, C3.1, C4.1 (+), C6.1, IC2.1 (INPUT), IC6.1 (VDD)
+5V_ISO: C5.2, IC5.5 (VCC+), IC6.8 (VISO), R13.2
+12V: C1.1 (+), C2.1, D1.2, IC2.3 (OUTPUT), POWER_AND_TSAL_SIGNAL.3
AIR+_AUX_CONTACT_OUT: AUX_CONTACT.3, POWER_AND_TSAL_SIGNAL.4, R1.2
AIR-_AUX_CONTACT_OUT: AUX_CONTACT.2, POWER_AND_TSAL_SIGNAL.5, R15.2
GND: C1.2 (-), C2.2, C3.2, C4.2 (-), C6.2, D1.1, IC2.4 (GND), IC6.4 (GND), POWER_AND_TSAL_SIGNAL.2, R1.1, R15.1, R16.1
HV+: HV+.1, HV+.2, R2.1
HV-: C5.1, HV-.1, HV-.2, IC5.2 (VCC-), IC6.5 (GNDISO), R11.1, R12.1
unnamed: R2.2, R3.1
unnamed: R3.2, R4.1
unnamed: R4.2, R5.2
unnamed: R5.1, R6.2
unnamed: R6.1, R7.2
unnamed: R7.1, R8.1
unnamed: R8.2, R9.1
unnamed: R9.2, R10.1
unnamed: IC5.4 (IN+), R10.2, R11.2
unnamed: IC5.3 (IN-), R12.2, R13.1
PRE_AUX_CONTACT_OUT: AUX_CONTACT.1, POWER_AND_TSAL_SIGNAL.6, R16.2
VOLTAGE_ON_ACCUMULATOR: IC6.2 (VOA), POWER_AND_TSAL_SIGNAL.1
VOLTAGE_ON_ACCUMULATOR_ISO: IC5.1 (OUT), IC6.7 (VIA)

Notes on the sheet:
Connector
12Vdc-5Vdc converter
Accumulator voltage measurement
Isolation
AIR & Precharge relays state
